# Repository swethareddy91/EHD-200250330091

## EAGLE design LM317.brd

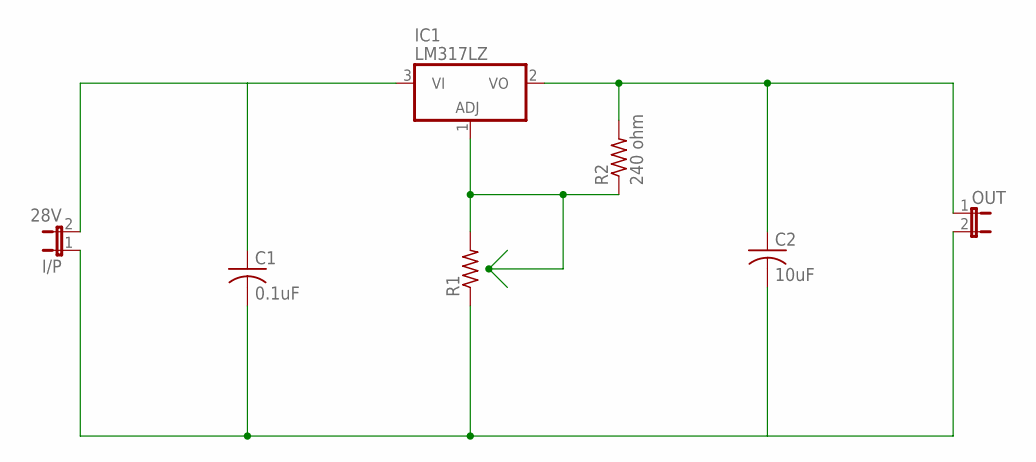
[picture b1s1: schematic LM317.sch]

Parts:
C1: 0.1uF; C025-025X050
C2: 10uF; C025-025X050
I/P: 28V; JP1
IC1: LM317LZ; TO92
OUT: JP1E; JP1
R1: R-US_0204/7; 0204/7
R2: 240 ohm; 0204/7

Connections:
unnamed: C1.1, I/P.2, IC1.3 (VI)
unnamed: C2.1, IC1.2 (VO), OUT.1, R2.2
unnamed: IC1.1 (ADJ), R1.2, R2.1
unnamed: C1.2, C2.2, I/P.1, OUT.2, R1.1

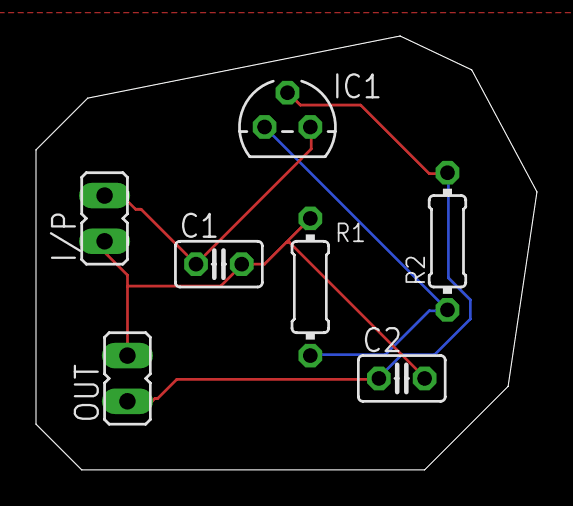
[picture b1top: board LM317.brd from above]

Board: 2 copper layers, 27.8 x 24.1 mm, 7 parts (0 on the bottom side), 4 nets.

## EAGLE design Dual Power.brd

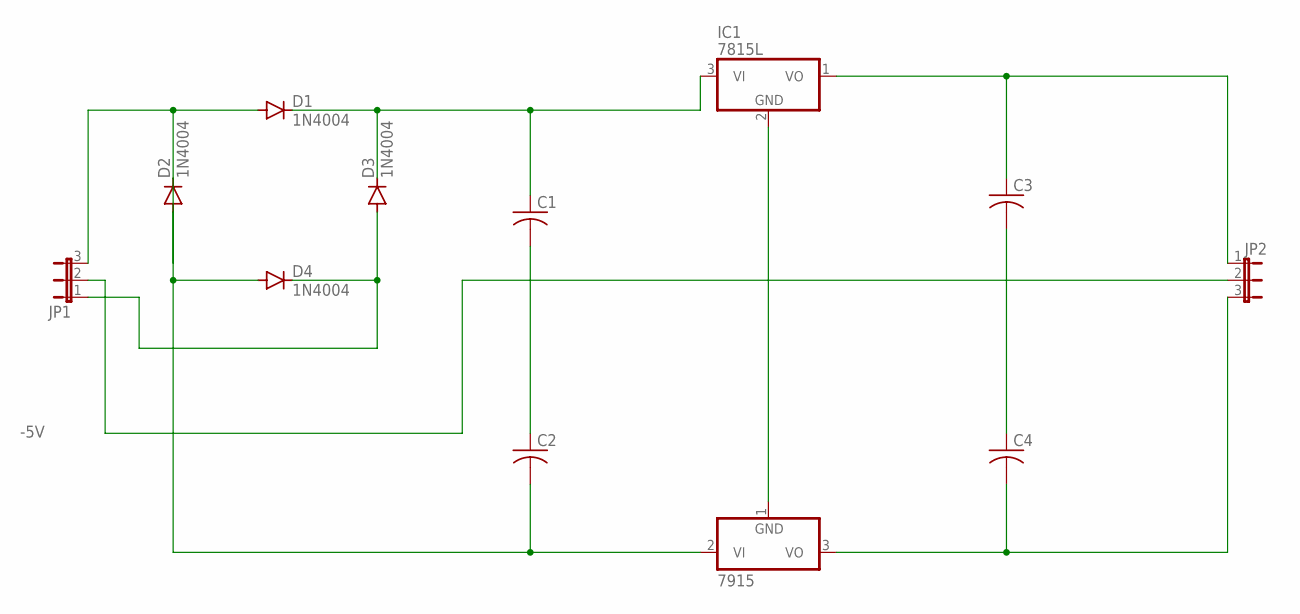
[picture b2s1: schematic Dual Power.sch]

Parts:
7915: 7915L; TO92
C1, C2, C3, C4: C-US025-025X050; C025-025X050
D1, D2, D3, D4: 1N4004; DO41-10
IC1: 7815L; TO92
JP1: JP2E; JP2
JP2: -5V; JP2

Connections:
unnamed: D3.A, D4.C, JP1.1
unnamed: D1.A, D2.C, JP1.3
unnamed: C1.1, D1.C, D3.C, IC1.3 (VI)
unnamed: JP1.2, JP2.2
unnamed: 7915.1 (GND), IC1.2 (GND)
unnamed: C1.2, C2.1
unnamed: C3.1, IC1.1 (VO), JP2.1
unnamed: 7915.3 (VO), C4.2, JP2.3
unnamed: C3.2, C4.1
unnamed: 7915.2 (VI), C2.2, D2.A, D4.A

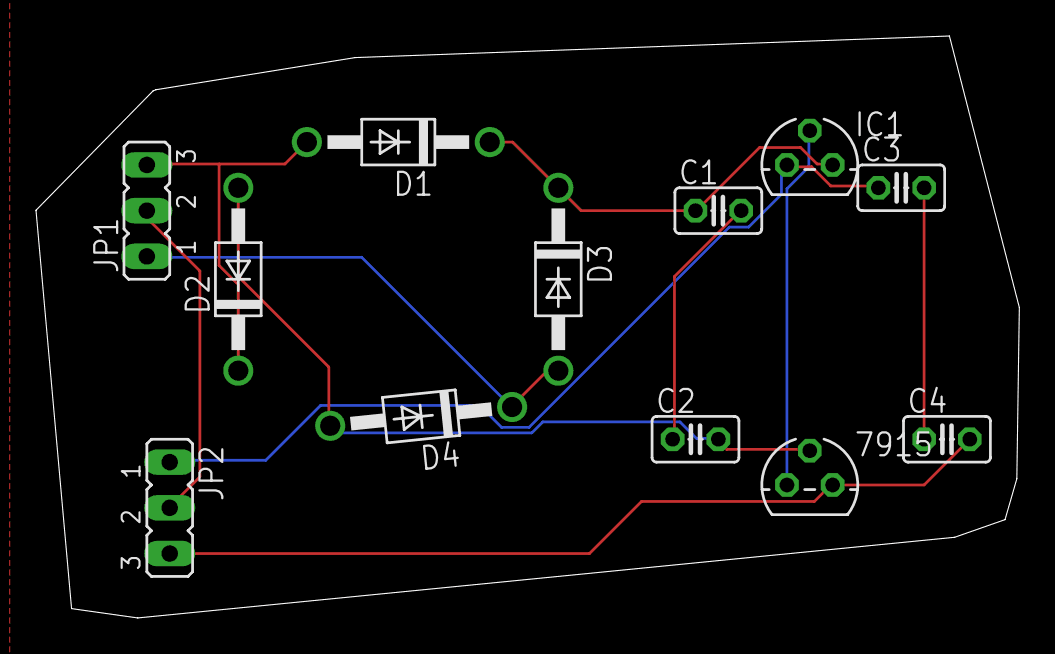
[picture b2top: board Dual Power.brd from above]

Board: 2 copper layers, 54.6 x 32.3 mm, 12 parts (0 on the bottom side), 10 nets.

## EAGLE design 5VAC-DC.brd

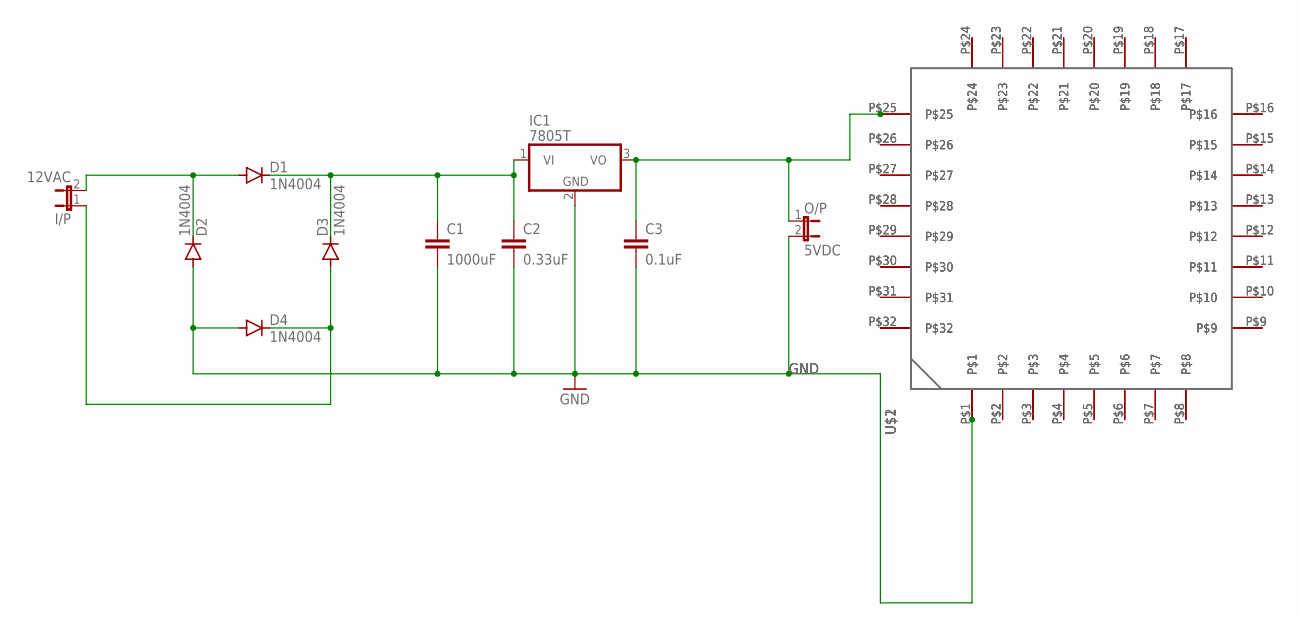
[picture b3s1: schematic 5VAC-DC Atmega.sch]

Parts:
C1: 1000uF; C2.5-3
C2: 0.33uF; C2.5-3
C3: 0.1uF; C2.5-3
D1, D2, D3, D4: 1N4004; DO41-10
I/P: 12VAC; JP1
IC1: 7805T; TO220H
O/P: 5VDC; JP1
U$1, U$2: MEGA8L-DEV; TQFP-MEGA8L

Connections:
GND: C1.2, C2.2, C3.2, D2.A, D4.A, IC1.2 (GND), O/P.2, U$1.P$1, U$2.P$1
unnamed: D1.A, D2.C, I/P.2
unnamed: U$1.P$2, U$2.P$2
unnamed: U$1.P$3, U$2.P$3
unnamed: C1.1, C2.1, D1.C, D3.C, IC1.1 (VI)
unnamed: C3.1, IC1.3 (VO), O/P.1, U$1.P$25, U$2.P$25
unnamed: U$1.P$4, U$2.P$4
unnamed: D3.A, D4.C, I/P.1
unnamed: U$1.P$5, U$2.P$5
unnamed: U$1.P$6, U$2.P$6
unnamed: U$1.P$7, U$2.P$7
unnamed: U$1.P$8, U$2.P$8
unnamed: U$1.P$9, U$2.P$9
unnamed: U$1.P$10, U$2.P$10
unnamed: U$1.P$11, U$2.P$11
unnamed: U$1.P$12, U$2.P$12
unnamed: U$1.P$13, U$2.P$13
unnamed: U$1.P$14, U$2.P$14
unnamed: U$1.P$15, U$2.P$15
unnamed: U$1.P$16, U$2.P$16
unnamed: U$1.P$17, U$2.P$17
unnamed: U$1.P$18, U$2.P$18
unnamed: U$1.P$19, U$2.P$19
unnamed: U$1.P$20, U$2.P$20
unnamed: U$1.P$21, U$2.P$21
unnamed: U$1.P$22, U$2.P$22
unnamed: U$1.P$23, U$2.P$23
unnamed: U$1.P$24, U$2.P$24
unnamed: U$1.P$26, U$2.P$26
unnamed: U$1.P$27, U$2.P$27
unnamed: U$1.P$28, U$2.P$28
unnamed: U$1.P$29, U$2.P$29
unnamed: U$1.P$30, U$2.P$30
unnamed: U$1.P$31, U$2.P$31
unnamed: U$1.P$32, U$2.P$32

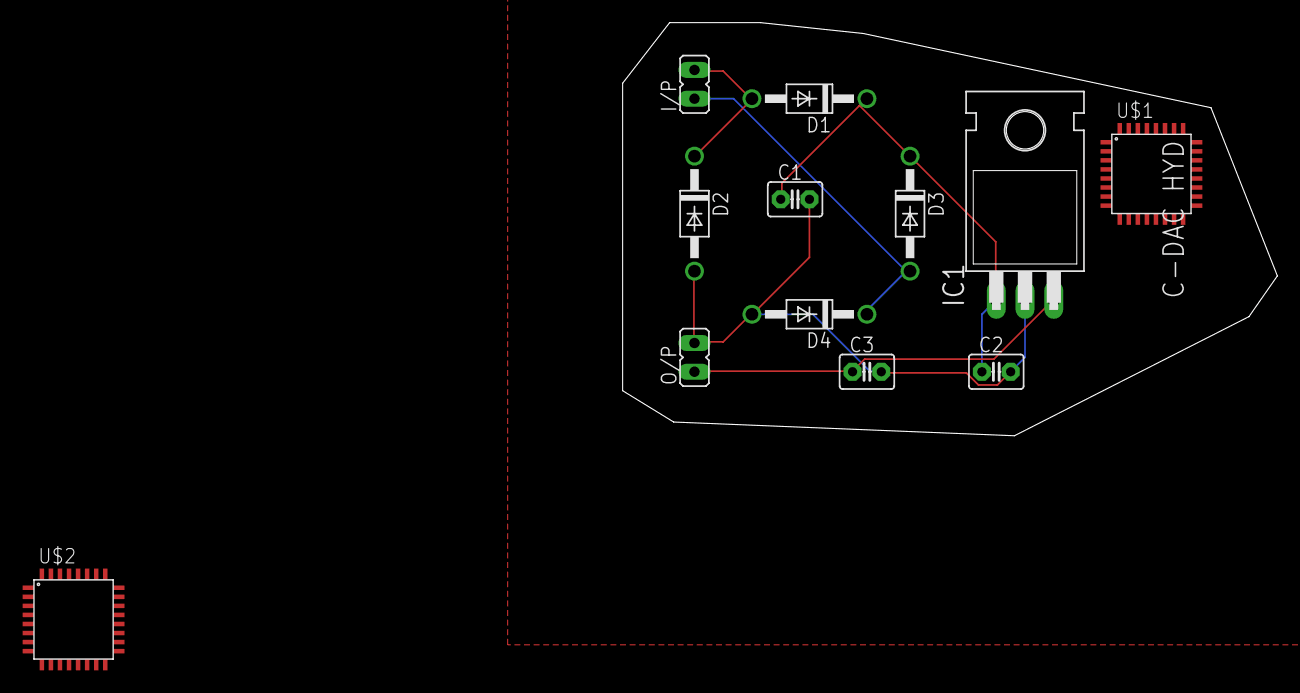
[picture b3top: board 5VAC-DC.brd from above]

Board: 2 copper layers, 57.9 x 36.5 mm, 12 parts (0 on the bottom side), 35 nets.

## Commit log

2020-10-06 Add files via upload
    sir i have done powersuppy board schematic ,after that i clicked on rectangle symbol so connections were disappeared n it becme green colour ..so i sent the image of the schematic which i have taken 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
